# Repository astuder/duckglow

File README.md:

# duckGLOW SAO

duckGLOW is an SAO with a glowing rubber duck, lit up by an RGB or UV LED,
controllable over I2C, or like an addressable LED following the WS2812
'standard'.

See [hackaday.io](https://hackaday.io/project/198918-duckglow-sao) for more
information.

See [examples folder](./examples) for sample code to run on the SuperCon 8
SAO badge, or an Arduino.

I have a few assembled units of the duckJAWS variant for sale on [Tindie](https://www.tindie.com/products/astuder/duckjaws-sao/).

## I2C Interface

The LED of the duckGLOW SAO can be controlled over I2C. 

The SAO has four channels: red, green and blue for the duck LED, and on the
duckJAWS variant, red background lightning.

The SAO implements smooth fading configurable per channel. The LED brightness
fades between **max** and **min** value, at the chosen **speed**. If speed is 0,
the LED will steadily glow at the configured maximum. The **phase** parameter
sets the offset in the fading waveform.

The **mode** register can be used to select the interface for LED control
(auto-detect, I2C or WS2812), and to check what type of LED was detected
(RGB or UV). 

The current settings can be stored as power-on preset by writing decimal
**42** to the **save** register. The power-on presets can be factory reset by
writing **24** to the **save** register.

### I2C Address

The default I2C address of the duckGLOW SAO is *`0x6C`*. The address can be 
changed by closing solder jumpers on the back of the circuit board. 
|SJ1|SJ2|Address|
|-|-|-|
|O|O|0x6C|
|C|O|0x6D|
|O|C|0x6E|
|C|C|0x6F|

### I2C Registers

Register are accessed by first writing the 8-bit register address, and then
reading or writing register data. The register address will auto-increment
and multiple registers can be read or written within a single I2C transaction. 

For example to read the max RGB colors with an Arduino:
```
Wire.beginTransmission(0x6C);
Wire.write((uint8_t) 0xEC);
Wire.endTransmission(false);
Wire.requestFrom(0x6C, 3);
while (Wire.available()) {
  char c = Wire.read();
  Serial.println(c, HEX);
}
```

And to set the red LED to maximum brightness:

```
Wire.beginTransmission(0x6C);
Wire.write((uint8_t) 0xEC); // red led max brightness
Wire.write(0xff);
Wire.endTransmission();
Wire.beginTransmission(0x6C);
Wire.write((uint8_t) 0xF4); // animation speed
Wire.write(0x0);
Wire.endTransmission();
```

|address|name|description|
|-|-|-|
|0x00| docs | some info about the add-on |
|0xEC-EF | max | max brightness for red, green, blue and background channels |
|0xF0-F3| min | min brightness for red, green, blue and background  channels |
|0xF4-F7| speed | fading speed per channel, 0 = set LED to max value (no fading) |
|0xF8-FB| phase | offset within fading animation per channel |
|0xFC| mode | bits 0..1: LED ctrl 0=auto, 1=I2C, 2=WS2812<br>bit 4: LED type 0=RGB, 1=UV |
|0xFD| save | write 42 to save current register values as new default<br>write 24 for factory reset |
|0xFE| debug | error codes for debugging firmware |

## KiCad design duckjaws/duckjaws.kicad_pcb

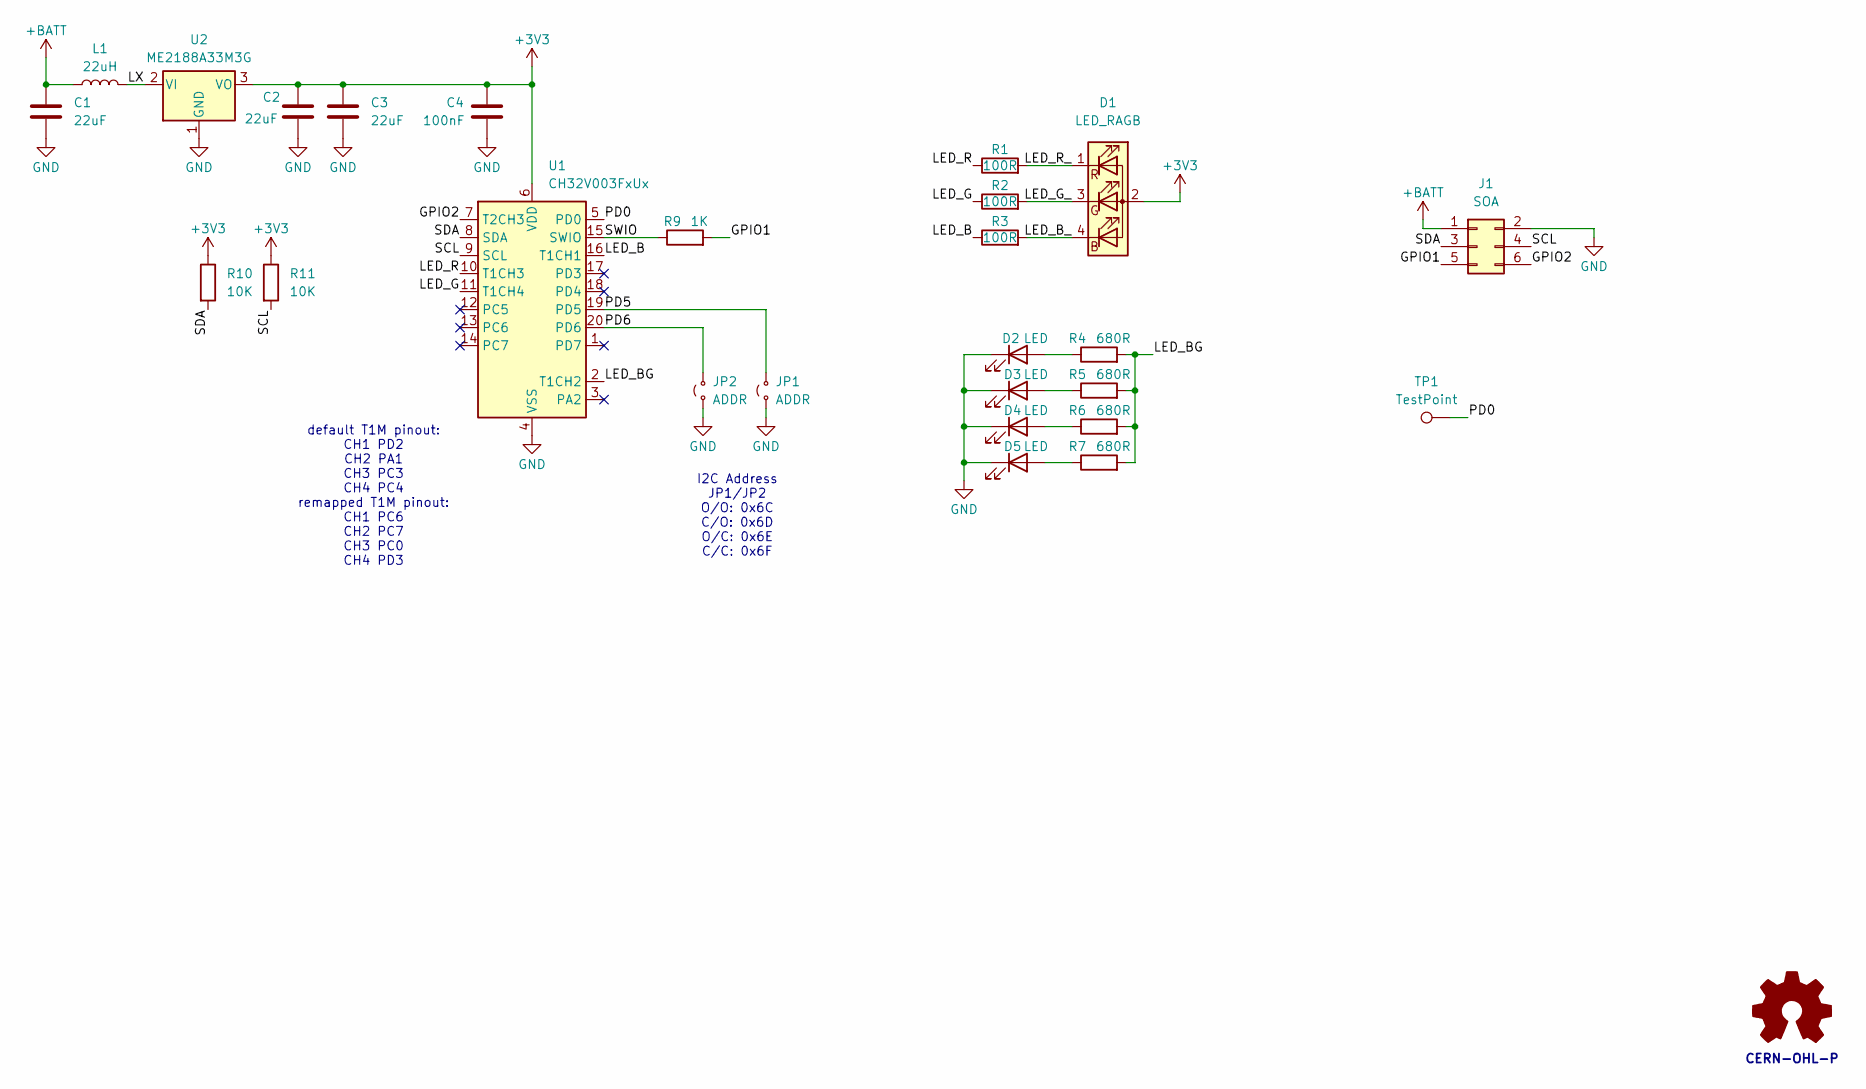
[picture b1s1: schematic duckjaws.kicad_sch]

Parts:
C1, C2, C3: 22uF; C_0805_2012Metric; LCSC C45783
C4: 100nF; C_0603_1608Metric; LCSC C14663
D1: LED_RAGB; LED_D5.0mm-4_RGB_single-side
D2, D3, D4, D5: LED; LED_Kingbright_APA1606_1.6x0.6mm_Horizontal; LCSC C409793
J1: SOA; PinHeader_2x03_P2.54mm_Vertical_SMD; LCSC C5160777
JP1, JP2: ADDR; SolderJumper-2_P1.3mm_Open_RoundedPad1.0x1.5mm
L1: 22uH; L_Changjiang_FNR3012S; LCSC C167732
R1, R2, R3: 100R; R_0603_1608Metric; LCSC C22775
R4, R5, R6, R7: 680R; R_0603_1608Metric; LCSC C23228
R9: 1K; R_0603_1608Metric; LCSC C21190
R10, R11: 10K; R_0603_1608Metric; LCSC C25804
TP1: TestPoint; TestPoint_Pad_D1.0mm
U1: CH32V003FxUx; QFN-20-1EP_3x3mm_P0.4mm_EP1.65x1.65mm; LCSC C5299908
U2: ME2188A33M3G; SOT-23; LCSC C111932

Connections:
+3V3: C2.1, C3.1, C4.1, D1.2 (A), R10.1, R11.1, U1.6 (VDD), U2.3 (VO)
+BATT: C1.1, J1.1, L1.1
/GPIO1: J1.5, R9.2
/GPIO2: J1.6, U1.7 (T2CH3)
/LED_B: R3.1, U1.16 (T1CH1)
/LED_BG: R4.2, R5.2, R6.2, R7.2, U1.2 (T1CH2)
/LED_B_: D1.4 (BK), R3.2
/LED_G: R2.1, U1.11 (T1CH4)
/LED_G_: D1.3 (GK), R2.2
/LED_R: R1.1, U1.10 (T1CH3)
/LED_R_: D1.1 (RK), R1.2
/LX: L1.2, U2.2 (VI)
/PD0: TP1.1, U1.5 (PD0)
/PD5: JP1.2 (B), U1.19 (PD5)
/PD6: JP2.2 (B), U1.20 (PD6)
/SCL: J1.4, R11.2, U1.9 (SCL)
/SDA: J1.3, R10.2, U1.8 (SDA)
/SWIO: R9.1, U1.15 (SWIO)
GND: C1.2, C2.2, C3.2, C4.2, D2.1 (K), D3.1 (K), D4.1 (K), D5.1 (K), J1.2, JP1.1 (A), JP2.1 (A), U1.4 (VSS), U1.21 (VSS), U2.1 (GND)
unnamed: D2.2 (A), R4.1
unnamed: D3.2 (A), R5.1
unnamed: D4.2 (A), R6.1
unnamed: D5.2 (A), R7.1

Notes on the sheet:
I2C Address JP1/JP2 O/O: 0x6C C/O: 0x6D O/C: 0x6E C/C: 0x6F
default T1M pinout: CH1 PD2 CH2 PA1 CH3 PC3 CH4 PC4 remapped T1M pinout: CH1 PC6 CH2 PC7 CH3 PC0 CH4 PD3
CERN-OHL-P

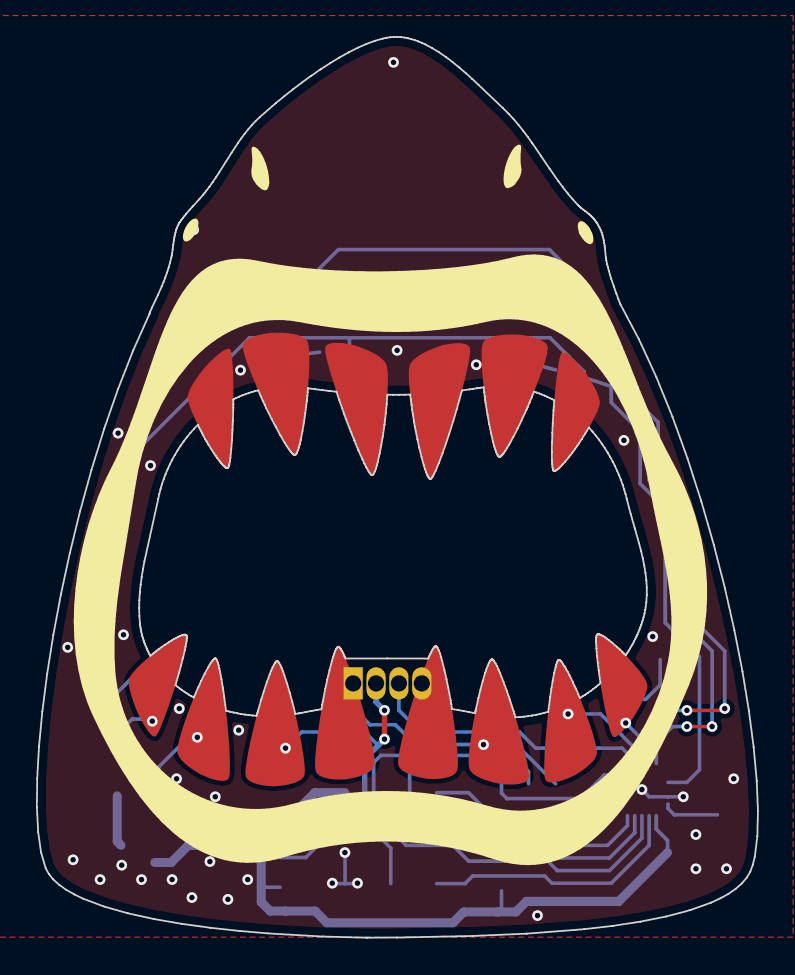
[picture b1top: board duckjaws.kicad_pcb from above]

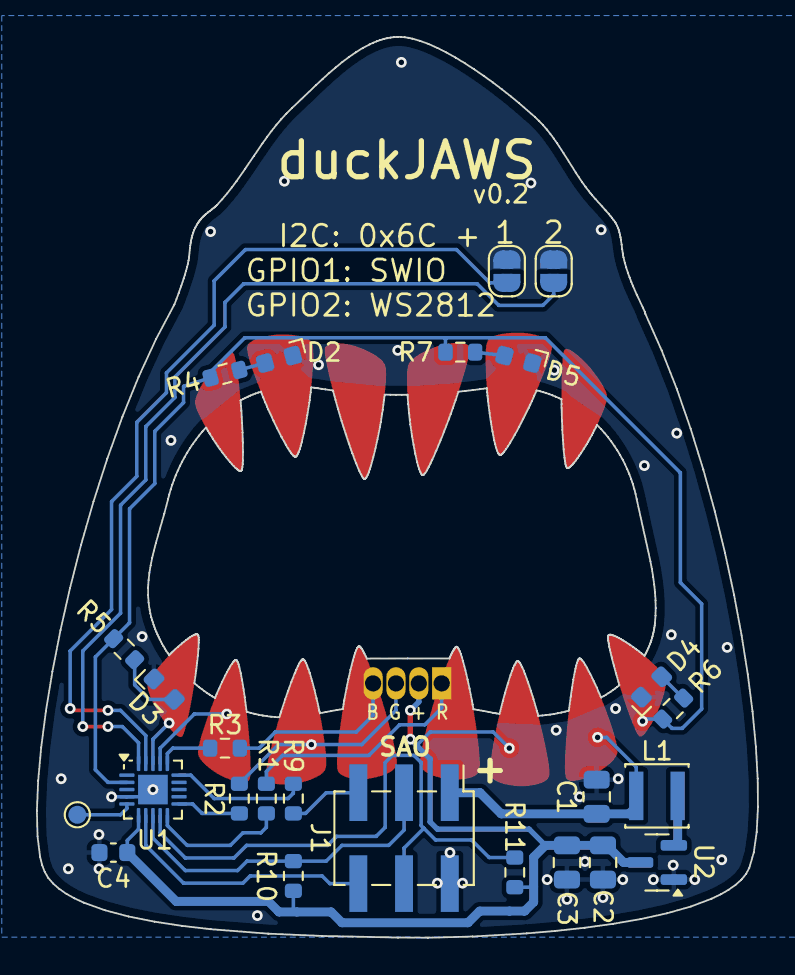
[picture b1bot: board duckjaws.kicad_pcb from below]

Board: 2 copper layers, 40.1 x 50.0 mm, 26 parts (25 on the bottom side), 23 nets.

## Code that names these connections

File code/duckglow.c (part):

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//	LED R: PC3, T1CH3, cathode (-)
//	LED G: PC4, T1CH4, cathode (-)
//	LED B: PD2, T1CH1, cathode (-)
#define LED_BG_PIN	PA1
#define LED_R_PIN	PC3
#define LED_G_PIN	PC4
#define LED_B_PIN	PD2

#define LED_BG_CH	2
#define LED_R_CH	3
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						RCC_APB2Periph_TIM1;
	
	// configure LED pins
	funPinMode(LED_BG_PIN, GPIO_CFGLR_OUT_10Mhz_AF_PP);
	funPinMode(LED_R_PIN, GPIO_CFGLR_OUT_10Mhz_AF_PP);
	funPinMode(LED_G_PIN, GPIO_CFGLR_OUT_10Mhz_AF_PP);
	funPinMode(LED_B_PIN, GPIO_CFGLR_OUT_10Mhz_AF_PP);

	// reset TIM1 to init all regs
	RCC->APB2PRSTR |= RCC_APB2Periph_TIM1;
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	funGpioInitAll();

	// enable pins routed test point and to lower right teeth, set them all low
	funPinMode(PD0, GPIO_CFGLR_OUT_10Mhz_PP);	// test point
	funPinMode(PD3, GPIO_CFGLR_OUT_10Mhz_PP);	// tooth, 2nd from right
	funPinMode(PD4, GPIO_CFGLR_OUT_10Mhz_PP);	// tooth, lower right 
	funDigitalWrite(PD0, 0);
	funDigitalWrite(PD3, 0);
	funDigitalWrite(PD4, 0);

	// set I2C address based on jumper configuration
	// PD5 connected to GND adds 1 to I2C_ADDR
	// PD6 connected to GND adds 2 to I2C_ADDR
	funPinMode(PD5, GPIO_CFGLR_IN_PUPD);
	funPinMode(PD6, GPIO_CFGLR_IN_PUPD);
	funDigitalWrite(PD5, 1);
	funDigitalWrite(PD6, 1);
	Delay_Ms(100);
	uint8_t i2c_addr = I2C_ADDR + (((funDigitalRead(PD6) << 1) + funDigitalRead(PD5)) ^ 3);

	// detect RGB LED on R pin with pull-down reads highish
	uv_led = 0;
	funPinMode(LED_R_PIN, GPIO_CFGLR_IN_PUPD);
	funDigitalWrite(LED_R_PIN, 1);	// start high to use 150mV schmitt trigger hystersis to over benefit
	Delay_Ms(10);
	funDigitalWrite(LED_R_PIN, 0);
	Delay_Ms(10);
	if (funDigitalRead(LED_R_PIN) == 0) {
		uv_led = 1;
	}

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
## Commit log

2024-10-19 add phase to LED fader registers
2024-10-19 auto-detect RGB or UV LED configuration
2024-10-20 add mode register
2024-10-20 fix RGB/UV auto-detect
2024-10-20 add photos
2024-10-27 implement WS2812 LED control
2024-10-27 prevent flash wear when repeatedly saving unchanged presets
2024-10-28 readme with detailed I2C documentation
2024-10-28 move readme to project root
2024-10-28 fix formatting
2024-10-28 reformat register table
2024-10-28 add PDFs of schematics
2024-10-28 replace register documentation with links to github and hackaday.io
2024-10-29 add factory reset function, fix saving of presets
2024-10-29 clarify description of some I2C registers
2024-10-30 make default animation bit brighter
2024-10-30 add sketch to test duck feature from an Arduino
2024-11-03 add examples
2024-11-03 add description to example
2024-11-03 link to examples
2024-11-03 add demo for I2C led control
2024-11-03 add demo to read text stored in duck
2025-01-13 add link to Tindie
2025-01-13 typo

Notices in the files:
duckjaws/duckjaws.kicad_pcb:
©2024 Adrian Studer
